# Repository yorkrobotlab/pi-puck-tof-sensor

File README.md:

# Time-of-Flight Distance Sensor for the Pi-puck

**A VL53L1X/VL53L0X time-of-flight distance sensor board for use with the Pi-puck robot platform.**

See https://github.com/yorkrobotlab/pi-puck for more information on the Pi-puck.

## PCB Layout

## Licence

Hardware designs are licensed under a [Creative Commons Attribution-ShareAlike 4.0 International Licence][cc-by-sa].

Unless otherwise specified, software is licensed under an [MIT Licence][mit].

[cc-by-sa]: http://creativecommons.org/licenses/by-sa/4.0/
[mit]: /LICENSE-MIT

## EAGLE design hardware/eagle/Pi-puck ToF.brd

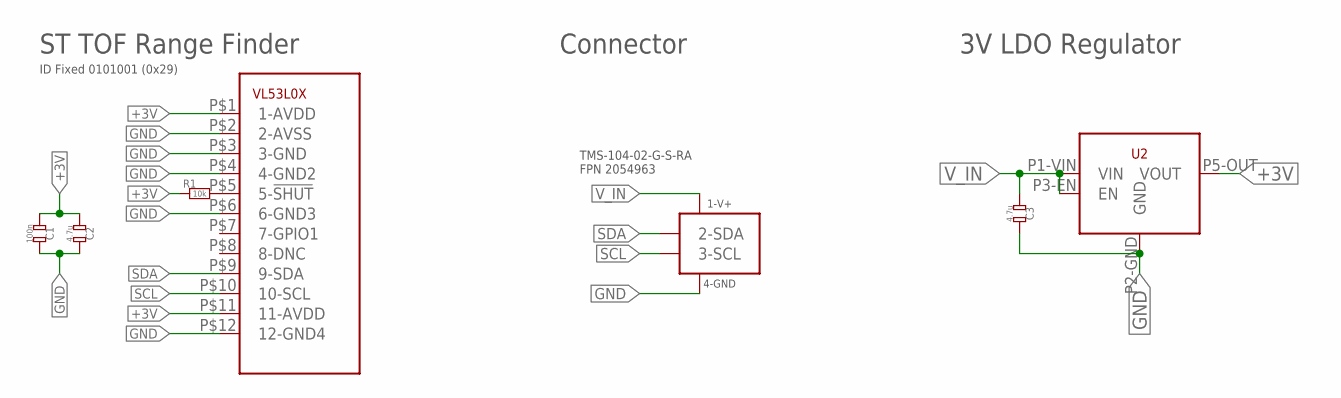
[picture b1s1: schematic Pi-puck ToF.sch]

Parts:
C1: 100n; 0603-RESISTOR
C2, C3: 4.7u; 0603-RESISTOR
R1: 10k; 0603-RESISTOR
SC1: 4-PIN-SENSOR-2054963-REVERSED; 4-PIN-0.05"-PITCH-THROUGH-HOLE-RA-SENSOR-REVERSED
U1: ST-VL53L0X; VL53L0X
U2: 2851575-LIC5365-LDO-3V-SC-70-5; MIC5365-3.0YC5-TR-SC70-5-LDO-VREG

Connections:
+3V: C1.1 (SD1), C2.1 (SD1), R1.1 (SD1), U1.P$1 (1-AVDD), U1.P$11 (11-AVDD), U2.P5-OUT (VOUT)
GND: C1.2 (SD2), C2.2 (SD2), C3.2 (SD2), SC1.1-GND (4-GND), U1.P$2 (2-AVSS), U1.P$3 (3-GND), U1.P$4 (4-GND2), U1.P$6 (6-GND3), U1.P$12 (12-GND4), U2.P2-GND (GND)
unnamed: R1.2 (SD2), U1.P$5 (5-!SHUT)
SCL: SC1.2-SCL (3-SCL), U1.P$10 (10-SCL)
SDA: SC1.3-SDA (2-SDA), U1.P$9 (9-SDA)
V_IN: C3.1 (SD1), SC1.4-V+ (1-V+), U2.P1-VIN (VIN), U2.P3-EN (EN)

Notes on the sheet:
TMS-104-02-G-S-RA FPN 2054963
ID Fixed 0101001 (0x29)
ST TOF Range Finder
Connector
3V LDO Regulator

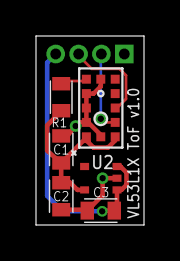
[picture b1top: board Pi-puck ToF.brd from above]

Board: 2 copper layers, 6.0 x 10.5 mm, 7 parts (1 on the bottom side), 6 nets.

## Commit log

2020-02-25 Added hardware design, and some info into the readme file
2020-02-27 Added Creative Commons licence for hardware designs
2020-02-28 Added MIT licence for any software code

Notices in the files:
parts and their libraries:
SparkFun-Aesthetics: Licensing: Creative Commons ShareAlike 4.0 International - https://creativecommons.org/licenses/by-sa/4.0
